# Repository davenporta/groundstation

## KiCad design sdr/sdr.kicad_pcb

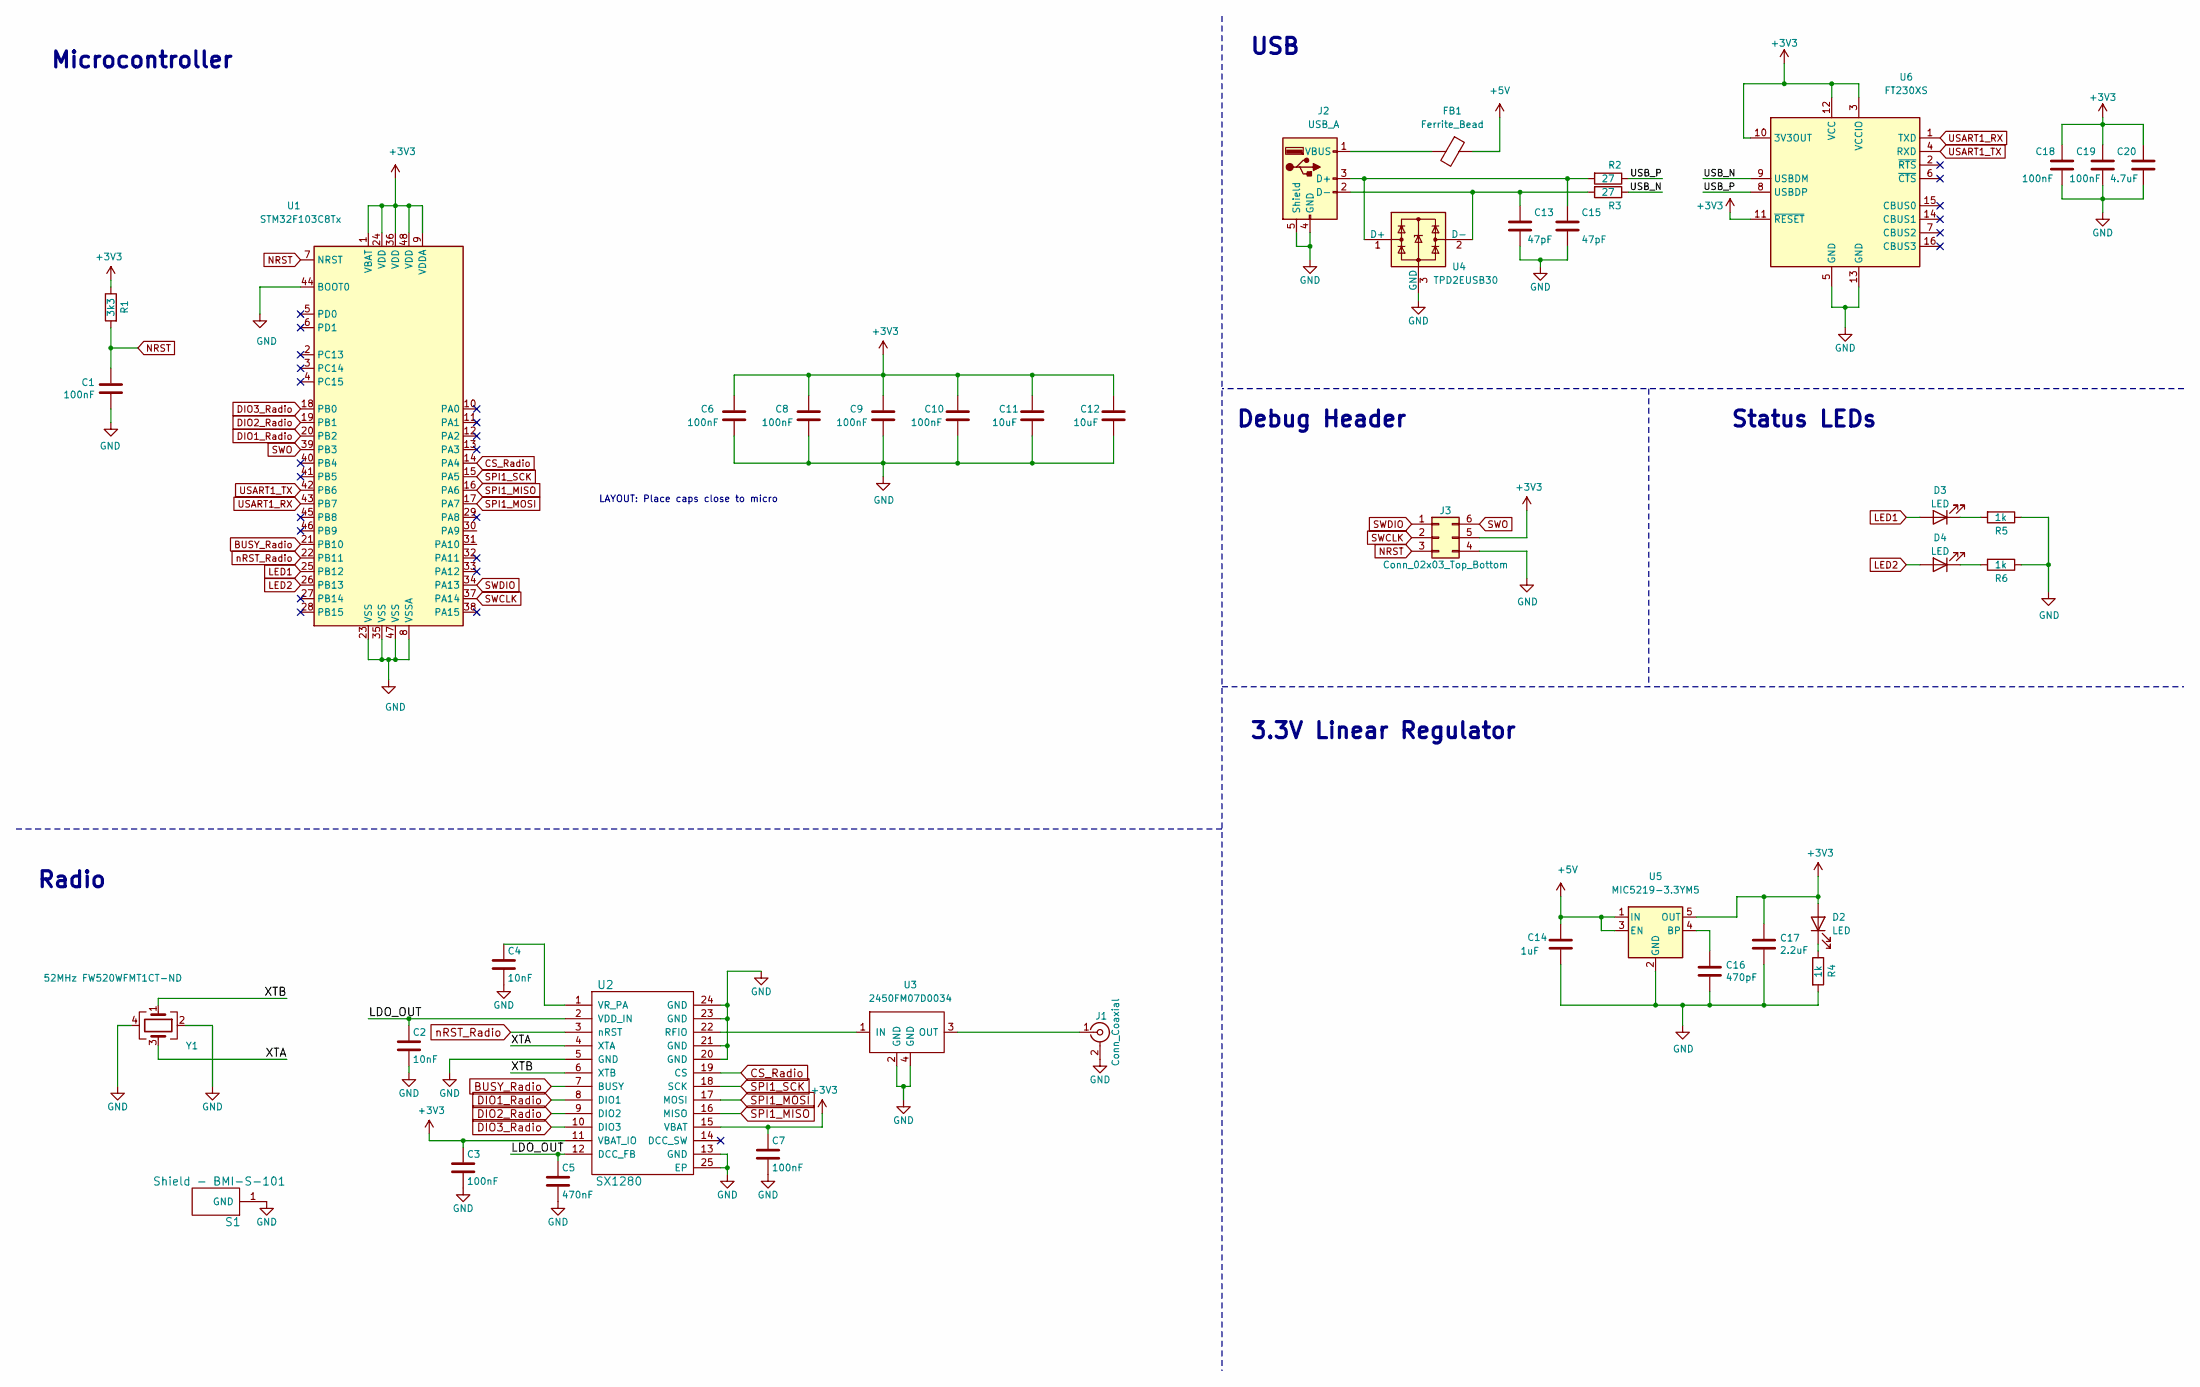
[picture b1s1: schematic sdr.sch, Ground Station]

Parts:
C1, C6, C8, C9, C10, C18, C19: 100nF; C_0603_1608Metric
C2, C4: 10nF; C_0402_1005Metric
C3, C7: 100nF; C_0402_1005Metric
C5: 470nF; C_0402_1005Metric
C11, C12: 10uF; C_0603_1608Metric
C13, C15: 47pF; C_0603_1608Metric
C14: 1uF; C_0603_1608Metric
C16: 470pF; C_0603_1608Metric
C17: 2.2uF; C_0603_1608Metric
C20: 4.7uF; C_0603_1608Metric
D2, D3, D4: LED; LED_0603_1608Metric
FB1: Ferrite_Bead; R_0603_1608Metric
J1: Conn_Coaxial; EBAY_SMA
J2: USB_A; 48037-0001
J3: Conn_02x03_Top_Bottom; PinHeader_2x03_P2.54mm_Vertical
R1: 3k3; R_0603_1608Metric
R2, R3: 27; R_0603_1608Metric
R4, R5, R6: 1k; R_0603_1608Metric
S1: Shield - BMI-S-101; Laird_Technologies_BMI-S-101_13.66x12.70mm
U1: STM32F103C8Tx; LQFP-48_7x7mm_P0.5mm
U2: SX1280; QFN-24-1EP_4x4mm_P0.5mm_EP2.6x2.6mm
U3: 2450FM07D0034; FIL_2450FM07D0034T
U4: TPD2EUSB30; Texas_DRT-3
U5: MIC5219-3.3YM5; SOT-23-5
U6: FT230XS; SSOP-16_3.9x4.9mm_P0.635mm
Y1: 52MHz FW520WFMT1CT-ND; Crystal_SMD_2016-4Pin_2.0x1.6mm

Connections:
+3V3: C3.1, C6.1, C7.1, C8.1, C9.1, C10.1, C11.1, C12.1, C17.1, C18.1, C19.1, C20.1, D2.2 (A), J3.5, R1.1, U1.1 (VBAT), U1.9 (VDDA), U1.24 (VDD), U1.36 (VDD), U1.48 (VDD), U2.11 (VBAT_IO), U2.15 (VBAT), U5.5 (OUT), U6.3 (VCCIO), U6.10 (3V3OUT), U6.11 (~RESET), U6.12 (VCC)
+5V: C14.1, FB1.1, U5.1 (IN), U5.3 (EN)
/LDO_OUT: C2.1, C5.1, U2.2 (VDD_IN), U2.12 (DCC_FB)
/USB_N: R3.1, U6.9 (USBDM)
/USB_P: R2.1, U6.8 (USBDP)
/XTA: U2.4 (XTA), Y1.3
/XTB: U2.6 (XTB), Y1.1
BUSY_Radio: U1.21 (PB10), U2.7 (BUSY)
CS_Radio: U1.14 (PA4), U2.19 (CS)
DIO1_Radio: U1.20 (PB2), U2.8 (DIO1)
DIO2_Radio: U1.19 (PB1), U2.9 (DIO2)
DIO3_Radio: U1.18 (PB0), U2.10 (DIO3)
GND: C1.2, C2.2, C3.2, C4.2, C5.2, C6.2, C7.2, C8.2, C9.2, C10.2, C11.2, C12.2, C13.2, C14.2, C15.2, C16.2, C17.2, C18.2, C19.2, C20.2, J1.2 (Ext), J2.4 (GND), J2.5 (Shield), J3.4, R4.2, R5.1, R6.1, S1.1, U1.8 (VSSA), U1.23 (VSS), U1.35 (VSS), U1.44 (BOOT0), U1.47 (VSS), U2.5 (GND), U2.13 (GND), U2.20 (GND), U2.21 (GND), U2.23 (GND), U2.24 (GND), U2.25 (EP), U3.2 (GND), U3.4 (GND), U4.3 (GND), U5.2 (GND), U6.5 (GND), U6.13 (GND), Y1.2, Y1.4
LED1: D3.2 (A), U1.25 (PB12)
LED2: D4.2 (A), U1.26 (PB13)
NRST: C1.1, J3.3, R1.2, U1.7 (NRST)
unnamed: C4.1, U2.1 (VR_PA)
unnamed: C13.1, J2.2 (D-), R3.2, U4.2 (D-)
unnamed: C15.1, J2.3 (D+), R2.2, U4.1 (D+)
unnamed: C16.1, U5.4 (BP)
unnamed: D2.1 (K), R4.1
unnamed: D3.1 (K), R5.2
unnamed: D4.1 (K), R6.2
unnamed: FB1.2, J2.1 (VBUS)
unnamed: J1.1 (In), U3.3 (OUT)
unnamed: U2.22 (RFIO), U3.1 (IN)
SPI1_MISO: U1.16 (PA6), U2.16 (MISO)
SPI1_MOSI: U1.17 (PA7), U2.17 (MOSI)
SPI1_SCK: U1.15 (PA5), U2.18 (SCK)
SWCLK: J3.2, U1.37 (PA14)
SWDIO: J3.1, U1.34 (PA13)
SWO: J3.6, U1.39 (PB3)
USART1_RX: U1.43 (PB7), U6.1 (TXD)
USART1_TX: U1.42 (PB6), U6.4 (RXD)
nRST_Radio: U1.22 (PB11), U2.3 (nRST)

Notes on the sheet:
3.3V Linear Regulator
Status LEDs
LAYOUT: Place caps close to micro
Debug Header
Microcontroller
Radio
USB

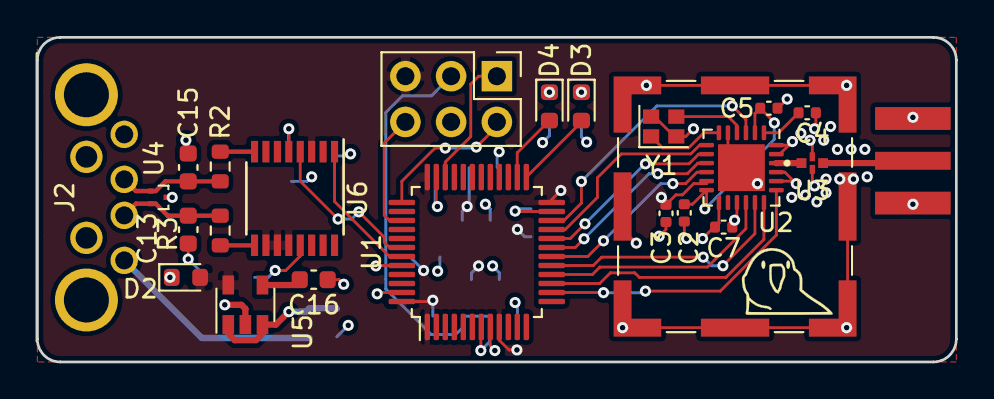
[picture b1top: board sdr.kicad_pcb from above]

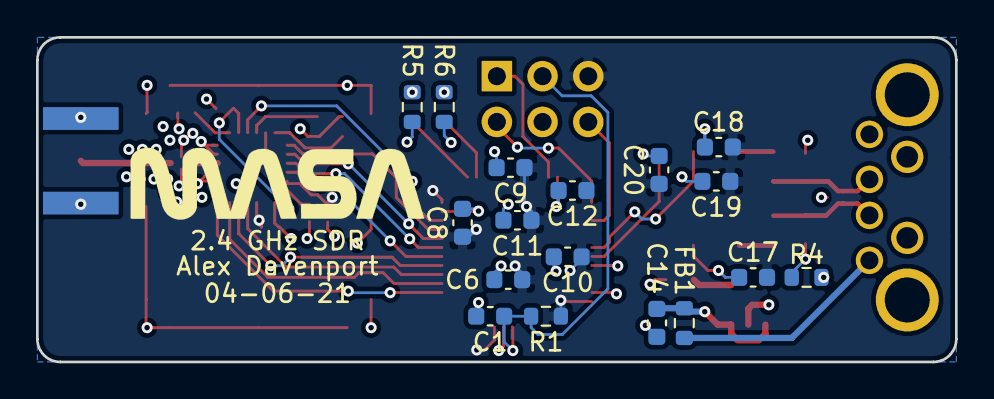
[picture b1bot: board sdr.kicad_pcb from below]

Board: 4 copper layers, 51.1 x 18.0 mm, 41 parts (17 on the bottom side), 35 nets.

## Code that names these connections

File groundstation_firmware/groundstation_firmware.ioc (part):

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Mcu.Name=STM32F103C(8-B)Tx
Mcu.Package=LQFP48
Mcu.UserName=STM32F103C8Tx
PA13.Mode=Trace_Asynchronous_SW
PA13.Signal=SYS_JTMS-SWDIO
PA14.Mode=Trace_Asynchronous_SW
PA14.Signal=SYS_JTCK-SWCLK
PA4.GPIOParameters=GPIO_Label
PA4.GPIO_Label=CS_Radio
PA4.Signal=GPIO_Output
PA5.Mode=Full_Duplex_Master
PA5.Signal=SPI1_SCK
PA6.Mode=Full_Duplex_Master
PA6.Signal=SPI1_MISO
PA7.Mode=Full_Duplex_Master
PA7.Signal=SPI1_MOSI
PB0.GPIOParameters=GPIO_Label
PB0.GPIO_Label=DIO3_Radio
PB0.Signal=GPXTI0
PB1.GPIOParameters=GPIO_Label
PB1.GPIO_Label=DIO2_Radio
PB1.Signal=GPXTI1
PB10.GPIOParameters=GPIO_Label
PB10.GPIO_Label=BUSY_Radio
PB10.Signal=GPIO_Input
PB11.GPIOParameters=GPIO_Label
PB11.GPIO_Label=nRST_Radio
PB11.Signal=GPIO_Output
PB12.GPIOParameters=GPIO_Label
PB12.GPIO_Label=LED1
PB12.Signal=GPIO_Output
PB13.GPIOParameters=GPIO_Label
PB13.GPIO_Label=LED2
PB13.Signal=GPIO_Output
PB2.GPIOParameters=GPIO_Label
PB2.GPIO_Label=DIO1_Radio
PB2.Signal=GPXTI2
PB3.Mode=Trace_Asynchronous_SW
PB3.Signal=SYS_JTDO-TRACESWO
PB6.Mode=Asynchronous
PB6.Signal=USART1_TX
PB7.Mode=Asynchronous
PB7.Signal=USART1_RX
board=custom

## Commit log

2021-07-20 ready for fab
